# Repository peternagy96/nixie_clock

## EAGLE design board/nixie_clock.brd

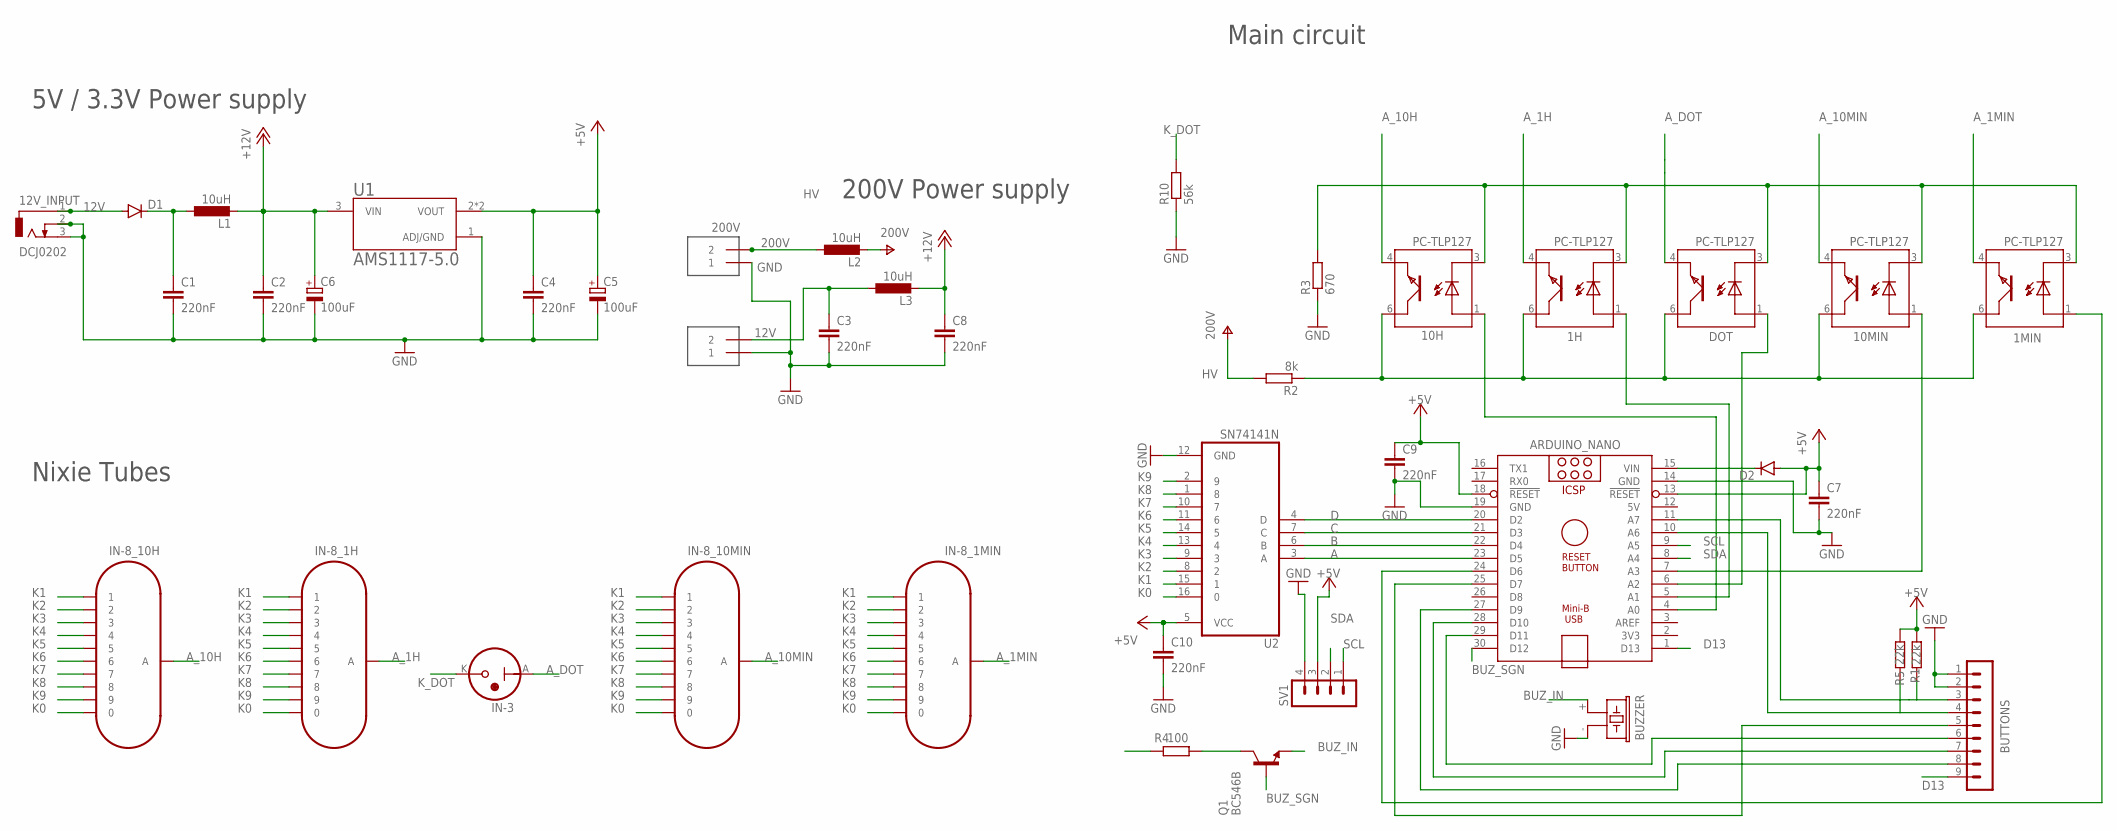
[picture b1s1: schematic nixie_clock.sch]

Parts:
1H, 1MIN, 10H, 10MIN: PC-TLP127; MINIFLAT4
12V, 200V: TERMINAL_2P; KF301-2P
12V_INPUT: DCJ0202
ARDUINO_NANO: ARDUINO_NANO
BUTTONS: MA09-1
BUZZER: F/CM12P
C1, C2, C3, C4, C7, C8, C9, C10: 220nF; C2.5-3
C5, C6: 100uF; E2,5-6E
D1, D2: 1N4148DO35-7; DO35-7
DOT: PC-TLP127; MINIFLAT4
IN-3: IN-3
IN-8_1H, IN-8_1MIN, IN-8_10H, IN-8_10MIN: IN-8
L1, L2, L3: 10uH; 0204/7
Q1: BC546B; TO92-EBC
R1, R5: 22k; 0204/7
R2: 8k; 0204/7
R3: 670; 0204/7
R4: 100; 0204/7
R10: 56k; 0204/7
SV1: MA04-1
U1: AMS1117-5.0; SOT229P700X180-4N
U2: SN74141N; DIP762W46P254L2134H508Q16

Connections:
5V: ARDUINO_NANO.12 (5V)
12V: 12V.2, 12V_INPUT.1, C3.1, D1.A, L3.1
200V: 200V.2, L2.1
+5V: ARDUINO_NANO.13 (!RESET), ARDUINO_NANO.18 (!RESET), C4.1, C5.+, C7.1, C9.1, C10.1, D2.A, R1.2, R5.2, SV1.3, U1.2 (VOUT), U1.4 (VOUT), U2.5 (VCC)
+12V: C2.1, C6.+, C8.1, L1.2, L3.2, R4.1, U1.3 (VIN)
A: ARDUINO_NANO.23 (D5), U2.3 (A)
A_1H: 1H.4 (TE), IN-8_1H.A
A_1MIN: 1MIN.4 (TE), IN-8_1MIN.A
A_10H: 10H.4 (TE), IN-8_10H.A
A_10MIN: 10MIN.4 (TE), IN-8_10MIN.A
A_DOT: DOT.4 (TE), IN-3.A
B: ARDUINO_NANO.22 (D4), U2.6 (B)
BUZ_IN: BUZZER.+ (1), Q1.E
BUZ_SGN: ARDUINO_NANO.30 (D12), Q1.B
C: ARDUINO_NANO.21 (D3), U2.7 (C)
D: ARDUINO_NANO.20 (D2), U2.4 (D)
D13: ARDUINO_NANO.1 (D13), BUTTONS.9
GND: 12V.1, 12V_INPUT.2, 12V_INPUT.3, 200V.1, ARDUINO_NANO.14 (GND), ARDUINO_NANO.19 (GND), BUTTONS.1, BUTTONS.2, BUZZER.- (2), C1.2, C2.2, C3.2, C4.2, C5.-, C6.-, C7.2, C8.2, C9.2, C10.2, R3.1, R10.1, SV1.4, U1.1 (ADJ/GND), U2.12 (GND)
HV: L2.2, R2.2
K0: IN-8_1H.0, IN-8_1MIN.0, IN-8_10H.0, IN-8_10MIN.0, U2.16 (0)
K1: IN-8_1H.1, IN-8_1MIN.1, IN-8_10H.1, IN-8_10MIN.1, U2.15 (1)
K2: IN-8_1H.2, IN-8_1MIN.2, IN-8_10H.2, IN-8_10MIN.2, U2.8 (2)
K3: IN-8_1H.3, IN-8_1MIN.3, IN-8_10H.3, IN-8_10MIN.3, U2.9 (3)
K4: IN-8_1H.4, IN-8_1MIN.4, IN-8_10H.4, IN-8_10MIN.4, U2.13 (4)
K5: IN-8_1H.5, IN-8_1MIN.5, IN-8_10H.5, IN-8_10MIN.5, U2.14 (5)
K6: IN-8_1H.6, IN-8_1MIN.6, IN-8_10H.6, IN-8_10MIN.6, U2.11 (6)
K7: IN-8_1H.7, IN-8_1MIN.7, IN-8_10H.7, IN-8_10MIN.7, U2.10 (7)
K8: IN-8_1H.8, IN-8_1MIN.8, IN-8_10H.8, IN-8_10MIN.8, U2.1 (8)
K9: IN-8_1H.9, IN-8_1MIN.9, IN-8_10H.9, IN-8_10MIN.9, U2.2 (9)
K_DOT: IN-3.K, R10.2
unnamed: ARDUINO_NANO.15 (VIN), D2.C
unnamed: C1.1, D1.C, L1.1
unnamed: 1MIN.1 (A), ARDUINO_NANO.24 (D6)
unnamed: ARDUINO_NANO.25 (D7), BUTTONS.5
unnamed: 1H.6 (TC), 1MIN.6 (TC), 10H.6 (TC), 10MIN.6 (TC), DOT.6 (TC), R2.1
unnamed: Q1.C, R4.2
unnamed: ARDUINO_NANO.10 (A6), BUTTONS.4, R5.1
unnamed: ARDUINO_NANO.11 (A7), BUTTONS.3, R1.1
unnamed: 10H.1 (A), ARDUINO_NANO.4 (A0)
unnamed: 1H.3 (C), 1MIN.3 (C), 10H.3 (C), 10MIN.3 (C), DOT.3 (C), R3.2
unnamed: ARDUINO_NANO.29 (D11), BUTTONS.6
unnamed: ARDUINO_NANO.28 (D10), BUTTONS.7
unnamed: ARDUINO_NANO.27 (D9), BUTTONS.8
unnamed: 1H.1 (A), ARDUINO_NANO.5 (A1)
unnamed: ARDUINO_NANO.6 (A2), DOT.1 (A)
unnamed: 10MIN.1 (A), ARDUINO_NANO.7 (A3)
SCL: ARDUINO_NANO.9 (A5), SV1.1
SDA: ARDUINO_NANO.8 (A4), SV1.2

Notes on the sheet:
5V / 3.3V Power supply
200V Power supply
Main circuit
Nixie Tubes

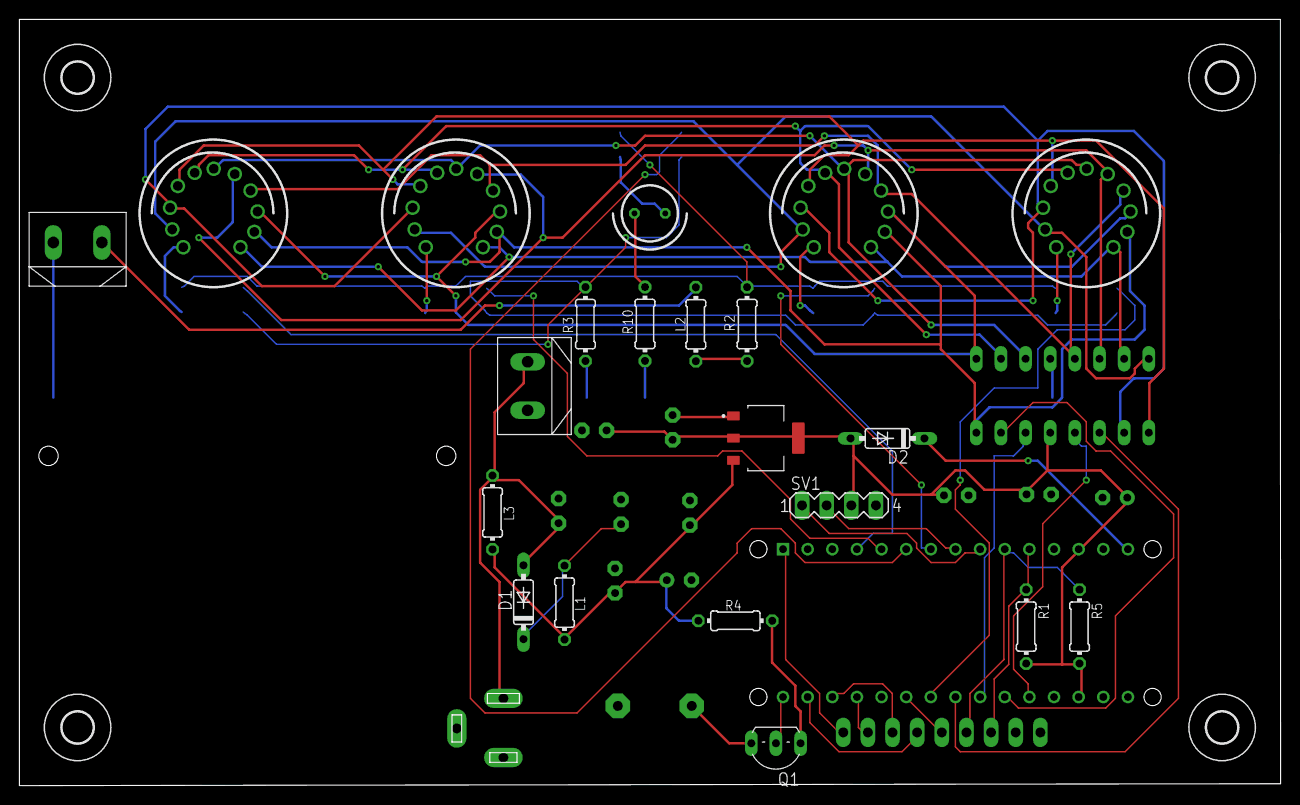
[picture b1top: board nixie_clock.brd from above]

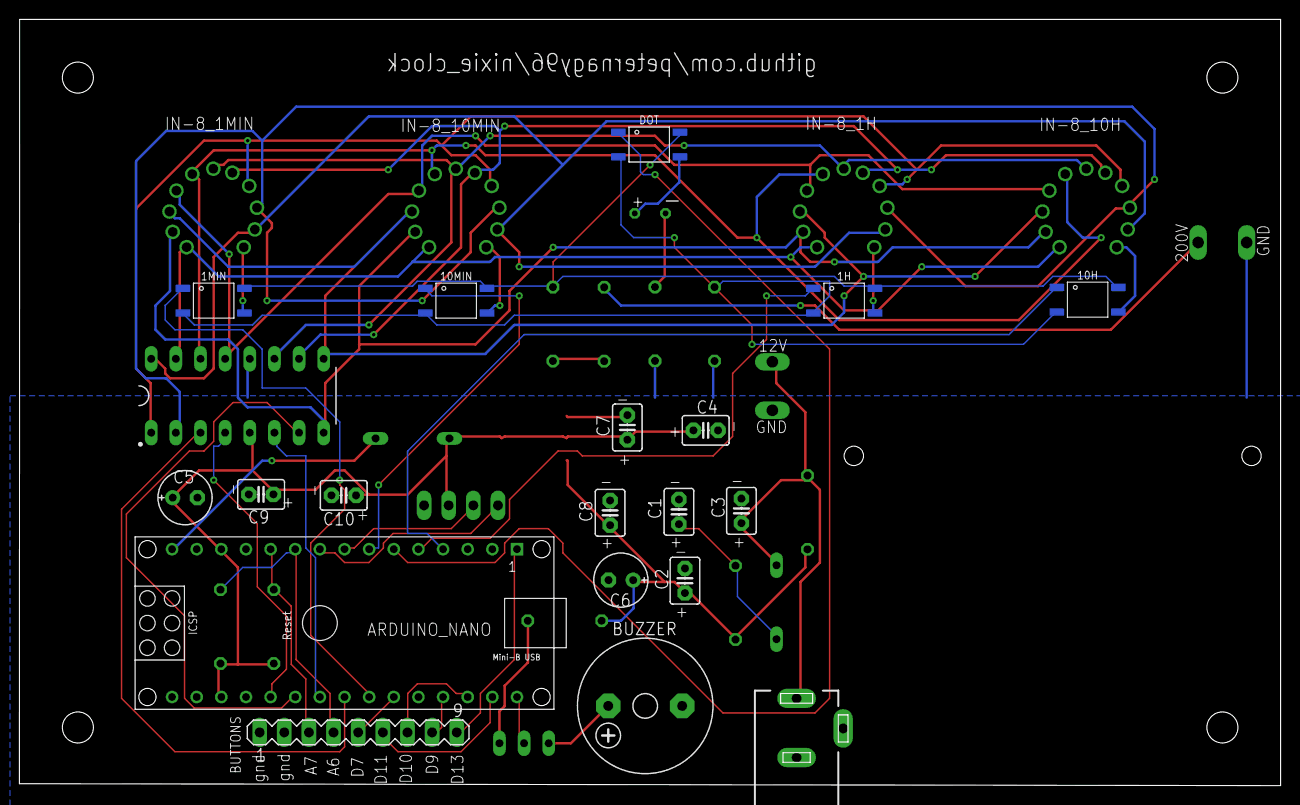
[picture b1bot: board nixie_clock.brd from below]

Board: 2 copper layers, 130.0 x 79.0 mm, 45 parts (20 on the bottom side), 47 nets.

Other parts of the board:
U$1, U$2, U$3, U$4: 3,2

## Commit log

2019-12-26 add readme
2020-01-08 removed auto-generated files
2020-01-08 added button to D13
2020-01-08 remove unnecessary files
2020-01-08 finalized board component layout
2020-01-08 moved the tubes towards the center
2020-01-09 ran autorouter with jlcpcb capabilities
2020-01-10 board design finalized
2020-01-10 added gerber file
2020-01-10 final board adjustments
2020-01-27 added unnecessary board files
2020-01-27 variable definitions + setup v0.1
2020-01-27 add cathode antipoising
2020-01-27 create files for all classes
2020-01-28 add RTCLib
2020-01-28 RTC imports
2020-01-28 add arduino config files
2020-01-28 add file for the alarm class
2020-01-28 basic display features implemented
2020-01-28 implement double blinking capability
2020-01-28 initialize classes
2020-01-28 rename file
2020-01-28 remove continuous longpress function
2020-01-28 added menu state machine logic
2020-01-28 controlChrono method added
2020-01-28 first refactor
2020-01-29 add abstract chrono class
2020-01-29 added set value functions
2020-01-29 add increment/decrement methdods
2020-01-29 implement inheritance from chrono
2020-01-29 fix roundup calculation
2020-01-29 inherits from ChronoClasss
2020-01-29 added inheritance from ChronoClass
2020-01-29 inherits from ChronoClass
2020-01-29 removed roundup
2020-01-29 added increment and decrement methods
2020-01-30 updated short month checking, removed stdlib
2020-01-30 format
2020-01-30 added #endif
2020-01-30 renamed methods to fit class name
2020-01-30 import chrono
2020-01-30 removed NIxieNumTubes_e struct
2020-01-30 fix syntax and include errors
2020-01-30 all compile errors fixed
2020-01-31 correct arduino pin numbers
2020-01-31 added buzzer and button pins
2020-01-31 added tubes test
2020-01-31 moved to new folder
2020-01-31 added alarm class
2020-01-31 updated tests
2020-02-01 check all tubes and numbers
2020-02-01 set arduino pins
2020-02-01 set RTC pins
2020-02-01 finalized tubes test
2020-02-01 finetuned tube duration
2020-02-01 added blinking
2020-02-03 tuned digit refresh frequency
2020-02-03 button test implemented
2020-02-03 added button press mechanism
2020-02-03 removed unnecessary function
2020-02-04 added tiltswitch mechanics
2020-02-04 update buzzer pin
2020-02-04 removed falling longpress method
2020-02-04 implemented buzzer
2020-02-04 added timekeeper implementation
2020-02-04 added warning to change RTC pins
2020-02-04 commented out rtc for testing
2020-02-05 implemented basic menu and timekeeping
2020-02-05 menu states implemented
2020-02-05 timekeeping with secTs implemented
2020-02-06 added hour setting
2020-02-06 all time keeping/setting features implemented
2020-02-06 all basic implementation - does not compile
2020-02-06 timekeeping works - still strange errors when setting time
2020-02-07 all main features work
2020-02-16 enable nixie dot
2020-02-16 PCB redesign
2020-02-16 move 200v header
2020-02-18 D13 pin added and minor placement changes
2020-02-19 Diode before Arduino's VIN added
2020-02-23 exported gerber of 2nd design
2020-06-14 board design v3
2020-06-15 rounded off 90 degree wire turns
2020-06-17 Connected 12V to buzzer.
2020-06-17 Exported board v3 gerber
2020-07-26 added nixie tube testing script.
2020-10-24 final version
2021-02-23 implement chess clock
2021-04-24 make sure button presses are not registered in rest mode
2021-04-24 change restmode time from 21 to midnight
2021-04-26 fix floating button
2021-09-05 add pomodoro timer
